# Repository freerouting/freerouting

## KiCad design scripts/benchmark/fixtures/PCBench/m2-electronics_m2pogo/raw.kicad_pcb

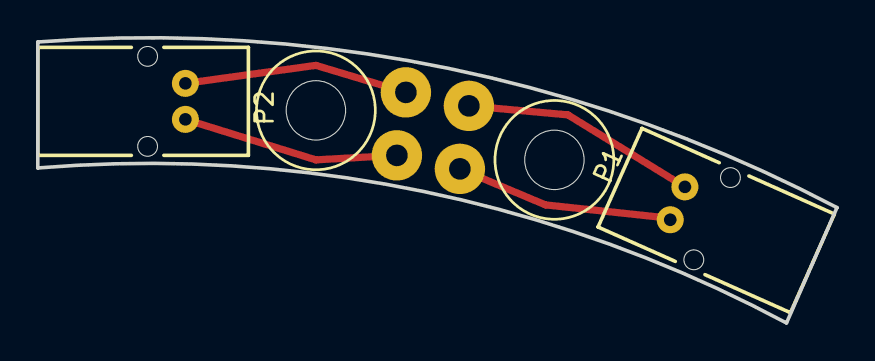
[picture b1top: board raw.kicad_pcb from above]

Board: 2 copper layers, 44.4 x 15.8 mm, 8 parts (0 on the bottom side), 4 nets.

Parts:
P1, P2: CONN_2; S02B-PASK-2
P3, P4, P5, P6: CONN_1; POGO
X3, X4: MOUNT; M3_MOUNT

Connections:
unnamed: P1.1, P4.1
unnamed: P1.2, P3.1
unnamed: P2.1, P6.1
unnamed: P2.2, P5.1

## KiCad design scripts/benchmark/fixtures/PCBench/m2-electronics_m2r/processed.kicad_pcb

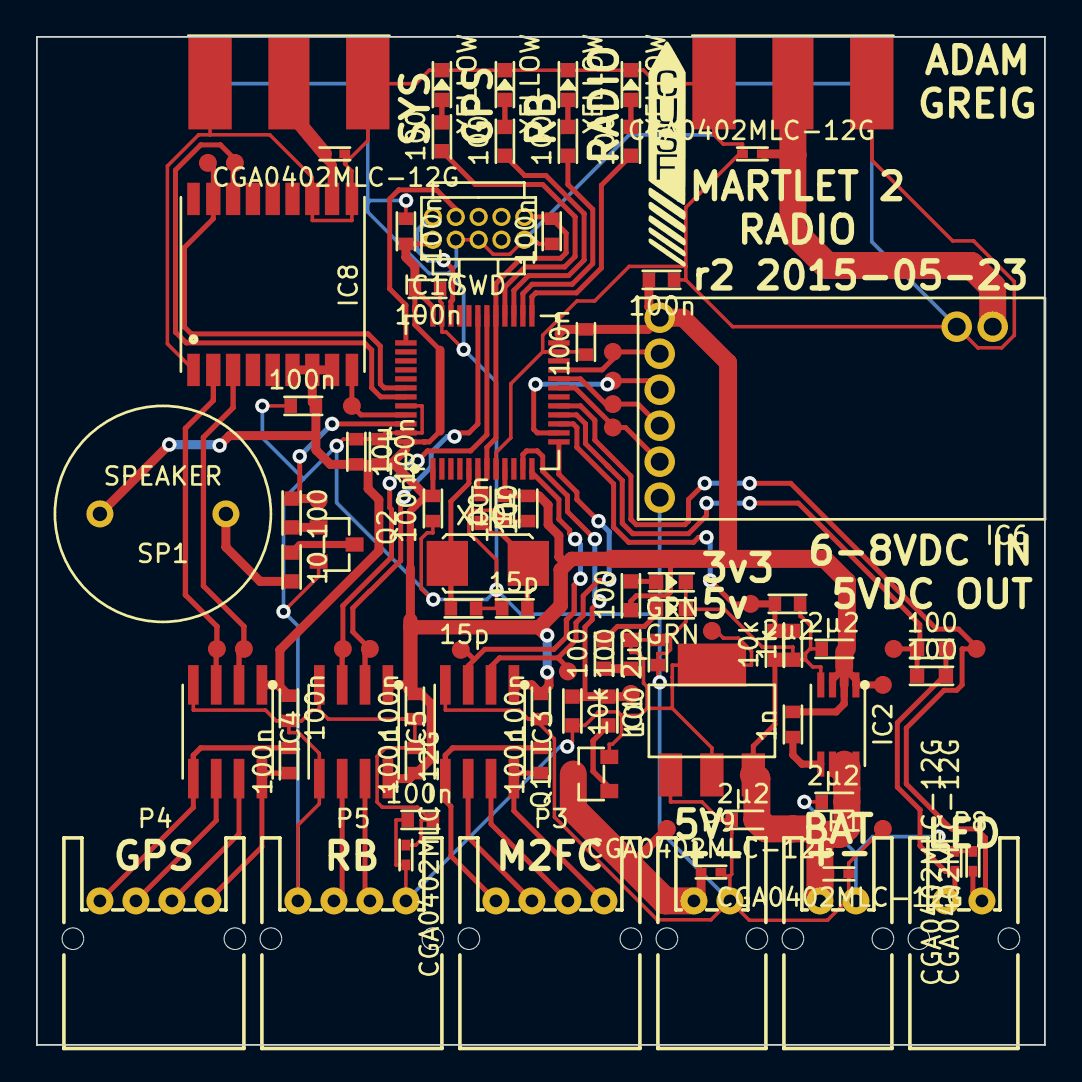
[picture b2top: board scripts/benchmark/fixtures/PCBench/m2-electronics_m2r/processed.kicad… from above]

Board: 2 copper layers, 56.0 x 56.0 mm, 99 parts (0 on the bottom side), 58 nets.

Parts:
C1, C2, C3, C4, C5, C6, C11, C14, C15, C24, C25, C26, C27, C29, C30, C34: 100n; C0603
C7, C8, C9, C10, C13: 2µ2; C0603
C12: 1n; C0603
C23: 10µ; C0603
C28: 1µ; C0603
C35, C36: 15p; C0603
D1, D2: GRN; LED0603
D3, D4, D5, D6: YELLOW; LED0603
D7, D8, D9, D10, D11, D12, D13: CGA0402MLC-12G; R0402
IC1: ADP3338; SOT223
IC2: ADP3335; MSOP8
IC3, IC4, IC5: ADuM1201; SOIC8
IC6: MTX2
IC8: MAX-7Q
IC10: STM32F303C; LQFP48
P1, P8, P9: CONN_2; S02B-PASK-2
P2, P7: SMA; SMA-142-0701-801
P3, P4, P5: CONN_4; S04B-PASK-2
P6: SWD; FTSH-105-01-F-D-K
Q1: Q_PMOS_GSD_PSV; SOT-23
Q2: Q_NMOS_GSD_PSV; SOT-23
R1, R3: 10k; R0603
R2: 1k; R0603
R4, R5, R7, R8, R9, R10, R11, R12, R13, R14, R15, R16: 100; R0603
R6: 10; R0603
SP1: SPEAKER; ABI-042-RC
TP1, TP2, TP4, TP7, TP11, TP12, TP13, TP14, TP15, TP16, TP17, TP18, TP19, TP20, TP21, TP22, TP23, TP24, TP25, TP26, TP27, TP28, TP29: TESTPAD
X10: 8M; XTAL50x32

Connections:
5V_OUT: IC10.11, R3.2, R16.2, TP27.1
+3V3: C3.2, C5.2, C6.1, C8.1, C11.1, C12.1, C14.1, C15.1, C23.1, C24.1, C25.1, C26.1, C27.1, C28.1, C29.1, C30.1, IC2.1, IC2.2, IC2.3, IC3.1, IC4.1, IC5.1, IC5.8, IC6.3, IC8.6, IC8.7, IC8.8, IC10.1, IC10.9, IC10.24, IC10.36, IC10.48, P6.1, R8.2, SP1.1, TP1.1
+5V: C4.2, C10.1, D7.1, IC1.2, P5.1, Q1.2, R3.1, R9.1, TP2.1
+BATT: C7.1, C9.1, D8.1, IC1.3, IC2.6, IC2.7, IC2.8, P1.2, R1.2, TP11.1
BAT_MON: C13.1, IC10.15, R1.1, R2.1, TP13.1
BUZZER: IC10.46, R15.2, TP28.1
GND: C3.1, C4.1, C5.1, C6.2, C7.2, C8.2, C9.2, C10.2, C11.2, C13.2, C14.2, C15.2, C23.2, C24.2, C25.2, C26.2, C27.2, C28.2, C29.2, C30.2, C34.2, C35.2, C36.2, D1.2, D2.2, D3.2, D4.2, D5.2, D6.2, D7.2, D8.2, D9.2, D10.1, D11.1, D12.2, D13.1, IC1.1, IC2.4, IC3.4, IC4.4, IC5.4, IC5.5, IC6.2, IC6.8, IC8.1, IC8.10, IC8.12, IC10.8, IC10.23, IC10.35, IC10.44, IC10.47, P1.1, P2.2, P2.3, P2.4, P2.5, P5.4, P6.3, P6.5, P6.9, P7.2, P7.3, P7.4, P7.5, P9.1, Q2.2, R2.2, TP12.1
GPS_RESET: IC8.9, IC10.45, TP19.1
GPS_RX: IC4.2, IC8.3, TP4.1
GPS_SCL: IC8.17, IC10.42, TP20.1
GPS_SDA: IC8.16, IC10.43, TP21.1
GPS_TX: IC4.3, IC8.2, TP7.1
LED_1: IC10.25, R10.2
LED_2: IC10.26, R12.2
LED_3: IC10.27, R11.2
LED_4: IC10.28, R13.2
LED_A: IC10.16, R4.2, R5.2, TP18.1
LED_C: D11.2, IC10.17, P8.1, TP26.1
NTX2B_EN: IC6.4, IC10.21, TP22.1
NTX2B_P0: IC6.7, IC10.19, TP25.1
NTX2B_P1: IC6.6, IC10.20, TP24.1
NTX2B_TXD: IC6.5, IC10.14, TP23.1
unnamed: C1.1, IC4.5, P4.4
unnamed: C1.2, IC4.8, P4.1
unnamed: C2.1, IC3.5, P3.4
unnamed: C2.2, IC3.8, P3.1
unnamed: C12.2, IC2.5
unnamed: C35.1, IC10.5, X10.1
unnamed: C36.1, R14.1, X10.2
unnamed: D1.1, R8.1
unnamed: D2.1, R7.1
unnamed: D3.1, R10.1
unnamed: D4.1, R11.1
unnamed: D5.1, R12.1
unnamed: D6.1, R13.1
unnamed: D9.1, IC6.1, P7.1
unnamed: D10.2, P8.2, R4.1, R5.1
unnamed: D12.1, IC8.11, P2.1
unnamed: D13.2, P9.2, Q1.3, TP29.1
unnamed: IC3.6, P3.3
unnamed: IC3.7, P3.2
unnamed: IC4.6, P4.3
unnamed: IC4.7, P4.2
unnamed: IC5.6, P5.3
unnamed: IC5.7, P5.2
unnamed: IC10.6, R14.2
unnamed: Q1.1, R16.1
unnamed: Q2.1, R15.1
unnamed: Q2.3, R6.2
unnamed: R6.1, SP1.2
unnamed: R7.2, R9.2
RB_RX: IC5.3, IC10.30, TP14.1
RB_TX: IC5.2, IC10.31, TP15.1
SER_IN: IC3.2, IC10.13, TP17.1
SER_OUT: IC3.3, IC10.12, TP16.1
SWCLK: IC10.37, P6.4
SWDIO: IC10.34, P6.2
nRST: C34.1, IC10.7, IC10.29, P6.10

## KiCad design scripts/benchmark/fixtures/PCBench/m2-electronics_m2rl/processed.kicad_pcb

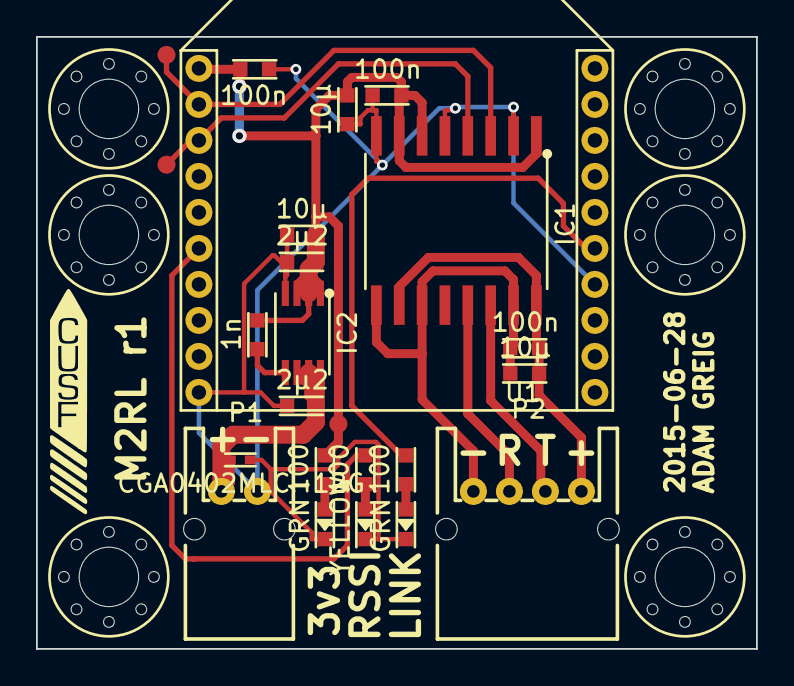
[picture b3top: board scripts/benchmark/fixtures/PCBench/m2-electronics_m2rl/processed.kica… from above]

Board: 2 copper layers, 40.0 x 34.0 mm, 30 parts (0 on the bottom side), 15 nets.

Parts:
C1, C7, C9: 10µ; C0603
C2, C3, C5: 100n; C0603
C4, C8: 2µ2; C0603
C6: 1n; C0603
D1: YELLOW; LED0603
D2: CGA0402MLC-12G; R0402
D3, D4: GRN; LED0603
IC1: ADuM5201; SOIC16W
IC2: ADP3335; MSOP8
M3_MOUNT, M3_MOUNT_2, M3_MOUNT_3, M3_MOUNT_4, M3_MOUNT_5, M3_MOUNT_6: VAL**; M3_MOUNT
P1: CONN_01X02; S02B-PASK-2
P2: CONN_01X04; S04B-PASK-2
R1, R2, R3: 100; R0603
TP3, TP4, TP5: TESTPAD
U1: XBEE

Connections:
+3V3: C1.1, C2.1, C3.1, C6.1, C8.1, C9.1, IC1.1, IC1.6, IC1.7, IC2.1, IC2.2, IC2.3, R3.1, TP5.1, U1.1
/DIN: IC1.4, TP4.1, U1.3
/DOUT: IC1.3, TP3.1, U1.2
GND: C1.2, C2.2, C3.2, C4.2, C8.2, C9.2, D1.1, D2.2, D3.1, D4.1, IC1.2, IC1.5, IC1.8, IC2.4, P1.1, U1.10, U1.14
unnamed: C4.1, D2.1, IC2.6, IC2.7, IC2.8, P1.2
unnamed: C5.1, C7.1, IC1.10, IC1.16, P2.1
unnamed: C5.2, C7.2, IC1.9, IC1.11, IC1.15, P2.4
unnamed: C6.2, IC2.5
unnamed: D1.2, R1.2
unnamed: D3.2, R2.2
unnamed: D4.2, R3.2
unnamed: IC1.13, P2.3
unnamed: IC1.14, P2.2
unnamed: R1.1, U1.6
unnamed: R2.1, U1.15
